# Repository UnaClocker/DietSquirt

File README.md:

# DietSquirt
Version 4.0 PCB Update October 2026
Migrated to KiCad 10.0, no more legacy Eagle requirements. The board is a 4 layer 100x100mm PCB now. Updated some components, 
switched to more common and standard sized components. As of the time of this writing, the boards are in production.
Included injector and coil drivers both this time. I know the injector drivers I picked will work with at least 2x 
high impedance injectors each.
I will update as needed with the results of the first test batch. Included the exact gerbers I submitted, but I have
made some minor changes to the silkscreen on the back of the PCB since then. One way or another, I'd like to have a 
functioning PCB to use in a vehicle in the next month, so this version will be fully tested here soon.
B&G actually sent me a cease and desist back when I first released this 10 years ago. Based on some obscure patent.
Well, it's been long enough that a patent would have expired by now. Given they started MegaSquirt around 2002, 
patents only last 17 years and it's going on 25 now... I kept the Anonymous name on there to keep up the rebel
spirit of this thing.
I still have a pile of MS1 CPU's, so this board is still 68hc908 centric. But a minor refactoring would make it 
perfectly happy with the MS2 CPU module or even MS3.

--- Old notes circa 2017 ---

Low cost DIY open source MegaSquirt derivative.

Welcome to my incomplete project. This was meant to be a much cheaper 
alternative to MegaSquirt. It uses the same processor as the MegaSquirt,
which is wired the same way as you might wire it for MegaSquirt-Extra 
firmware. Now being that this is not a licensed board, you shouldn’t run 
their firmware on it. But if you do, who am I to stop you. ;) You’re not 
supposed to run MegaSquirt on street cars either, but most MegaSquirt users 
do.

Please watch the video about this: https://www.youtube.com/watch?v=LJTZ3sH1d-M

This project is licensed under the BSD License. Take it and do anything with
it. If you mass produce and sell it, I hope you’re not using the MegaSquirt 
firmware, their lawyers will bury you. Your own personal use, totally another 
matter, not worth coming after Joe Blow who’s running it in their own car. 
Ideally, the MegaSquirt firmware can prove the board, then we can switch to 
a far better processor and far more open firmware like the STM32F4 with 
RusEFI firmware. I signed the board “Anonymous” because of the risk of 
B&G’s lawyers. 

As stated, this board is a work in progress. I’d like to say I can come 
back and finish it, but I designed it two years ago, maybe 2 1/2 years at 
this point. Right after that I discovered my wife was having an affair 
(TMI…), and entered a long drawn out divorce. Now I’m a single father of 
two kids so I don’t have much time to devote to these projects anymore. 
I’m placing the files on Github, we can work together to update and fix 
the board as testing progresses.
Current known issues: 
	The components for the voltage regulator circuit are too big and 
don’t fit. Namely the capacitors. 
	It needs the LC filter added between the output of the VR and the 
rest of the board to clean up the noise from the switch mode power supply. 
See the data sheet to the 34063 voltage regulator for that circuit.
	The DB15 and DB25 connectors are too far inboard, they need to be 
shifted out to the next mark on the silkscreen.

Next up, this board does not have onboard injector drivers. I had intended 
it to use the JBPerf P&H board. He seems to have stopped selling it since 
then, so I, or someone else may need to create a clone of his old board. 
It’s a very very simple circuit board to make. The chips are still available.

You can submit the .brd files to OSHPark.com to have 3 copies of the board 
made. It’s VERY expensive there. but if you’re in the US, they’re very fast. 
You can get 10 boards made at www.elecrow.com, under their 5cmx10cm pricing, 
I believe it’s $20 for 10 boards. Give the spare boards to friends, or save 
them as spares. Don’t sell them, you’ll risk the wrath of the B&G lawyers.

See the attached BOM for the list of parts you’ll want to order from Digikey 
for this board.

The files are for Eagle. Place the .brd and .sch files in a DietSquirt folder
under your main eagle projects, then load the .sch schematic file and .brd board 
layout file. The gerbers are included, but since the board needs work still, 
I wouldn't suggest building having it produced. At the very least, you'd have 
to run an external 5v voltage regulator. I'd have prefered to have done the 
board in KiCad, but I knew Eagle better at the time. You can get a free version 
of Eagle, google it, download it. Works in all 3 major OS's.

I’m probably forgetting a lot. I’ll document more as time allows. 
Questions? unaclocker@gmail.com

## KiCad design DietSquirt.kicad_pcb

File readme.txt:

Welcome to my incomplete project. This was meant to be a much cheaper 
alternative to MegaSquirt. It uses the same processor as the MegaSquirt,
which is wired the same way as you might wire it for MegaSquirt-Extra 
firmware. Now being that this is not a licensed board, you shouldn’t run 
their firmware on it. But if you do, who am I to stop you. ;) You’re not 
supposed to run MegaSquirt on street cars either, but most MegaSquirt users 
do.
Please watch the video about this which will be posted on YouTube shortly.
This project is licensed under the BSD License. Take it and do anything with
it. If you mass produce and sell it, I hope you’re not using the MegaSquirt 
firmware, their lawyers will bury you. Your own personal use, totally another 
matter, not worth coming after Joe Blow who’s running it in their own car. 
Ideally, the MegaSquirt firmware can prove the board, then we can switch to 
a far better processor and far more open firmware like the STM32F4 with 
RusEFI firmware. I signed the board “Anonymous” because of the risk of 
B&G’s lawyers. 
As stated, this board is a work in progress. I’d like to say I can come 
back and finish it, but I designed it two years ago, maybe 2 1/2 years at 
this point. Right after that I discovered my wife was having an affair 
(TMI…), and entered a long drawn out divorce. Now I’m a single father of 
two kids so I don’t have much time to devote to these projects anymore. 
I’m placing the files on Github, we can work together to update and fix 
the board as testing progresses.
Current known issues: 
	The components for the voltage regulator circuit are too big and 
don’t fit. Namely the capacitors. 
	It needs the LC filter added between the output of the VR and the 
rest of the board to clean up the noise from the switch mode power supply. 
See the data sheet to the 34063 voltage regulator for that circuit.
	The DB15 and DB25 connectors are too far inboard, they need to be 
shifted out to the next mark on the silkscreen.

Next up, this board does not have onboard injector drivers. I had intended 
it to use the JBPerf P&H board. He seems to have stopped selling it since 
then, so I, or someone else may need to create a clone of his old board. 
It’s a very very simple circuit board to make. The chips are still available.

You can submit the .brd files to OSHPark.com to have 3 copies of the board 
made. It’s VERY expensive there. but if you’re in the US, they’re very fast. 
You can get 10 boards made at www.elecrow.com, under their 5cmx10cm pricing, 
I believe it’s $20 for 10 boards. Give the spare boards to friends, or save 
them as spares. Don’t sell them, you’ll risk the wrath of the B&G lawyers.

See the attached BOM for the list of parts you’ll want to order from Digikey 
for this board.

The files are for Eagle. Load the .pro project file, then load the .sch 
schematic file and .brd board layout file. The gerbers are included, but 
since the board needs work still, I wouldn't suggest building it. At the 
very least, you'd have to run an external 5v voltage regulator. I'd have 
prefered to have done the board in KiCad,
but I knew Eagle better at the time. You can get a free version of Eagle, 
google it, download it. Works in all 3 major OS's.

I’m probably forgetting a lot. I’ll document more as time allows. 
Questions? unaclocker@gmail.com

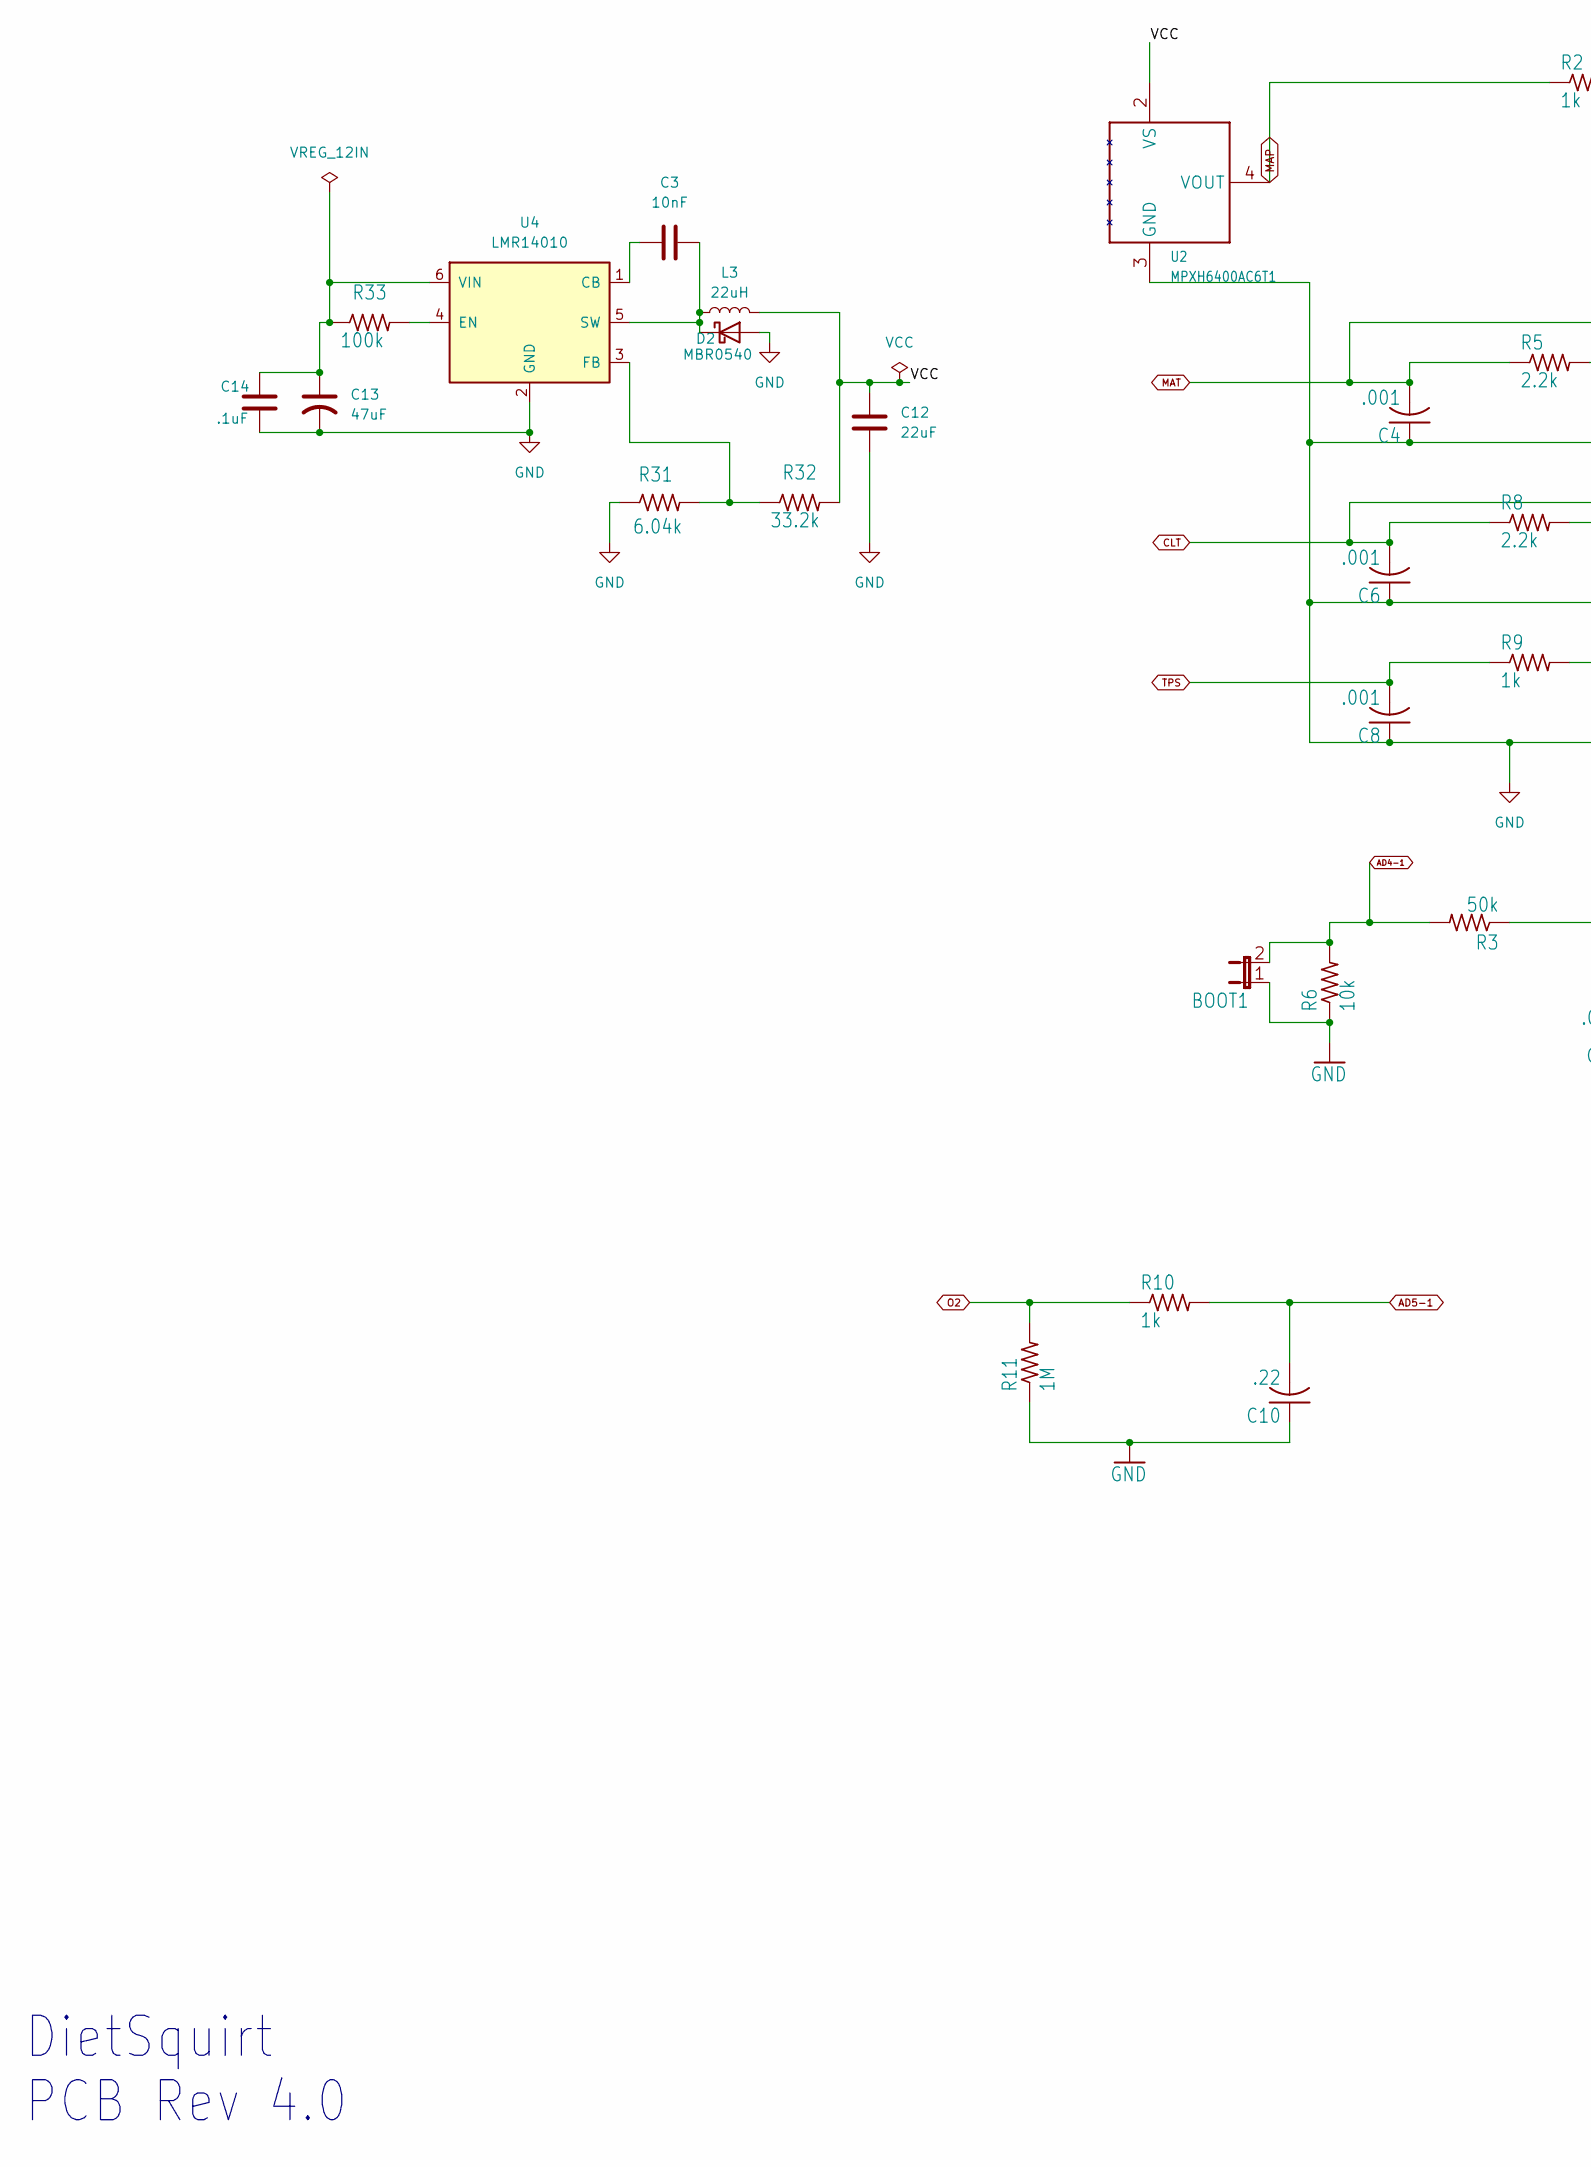
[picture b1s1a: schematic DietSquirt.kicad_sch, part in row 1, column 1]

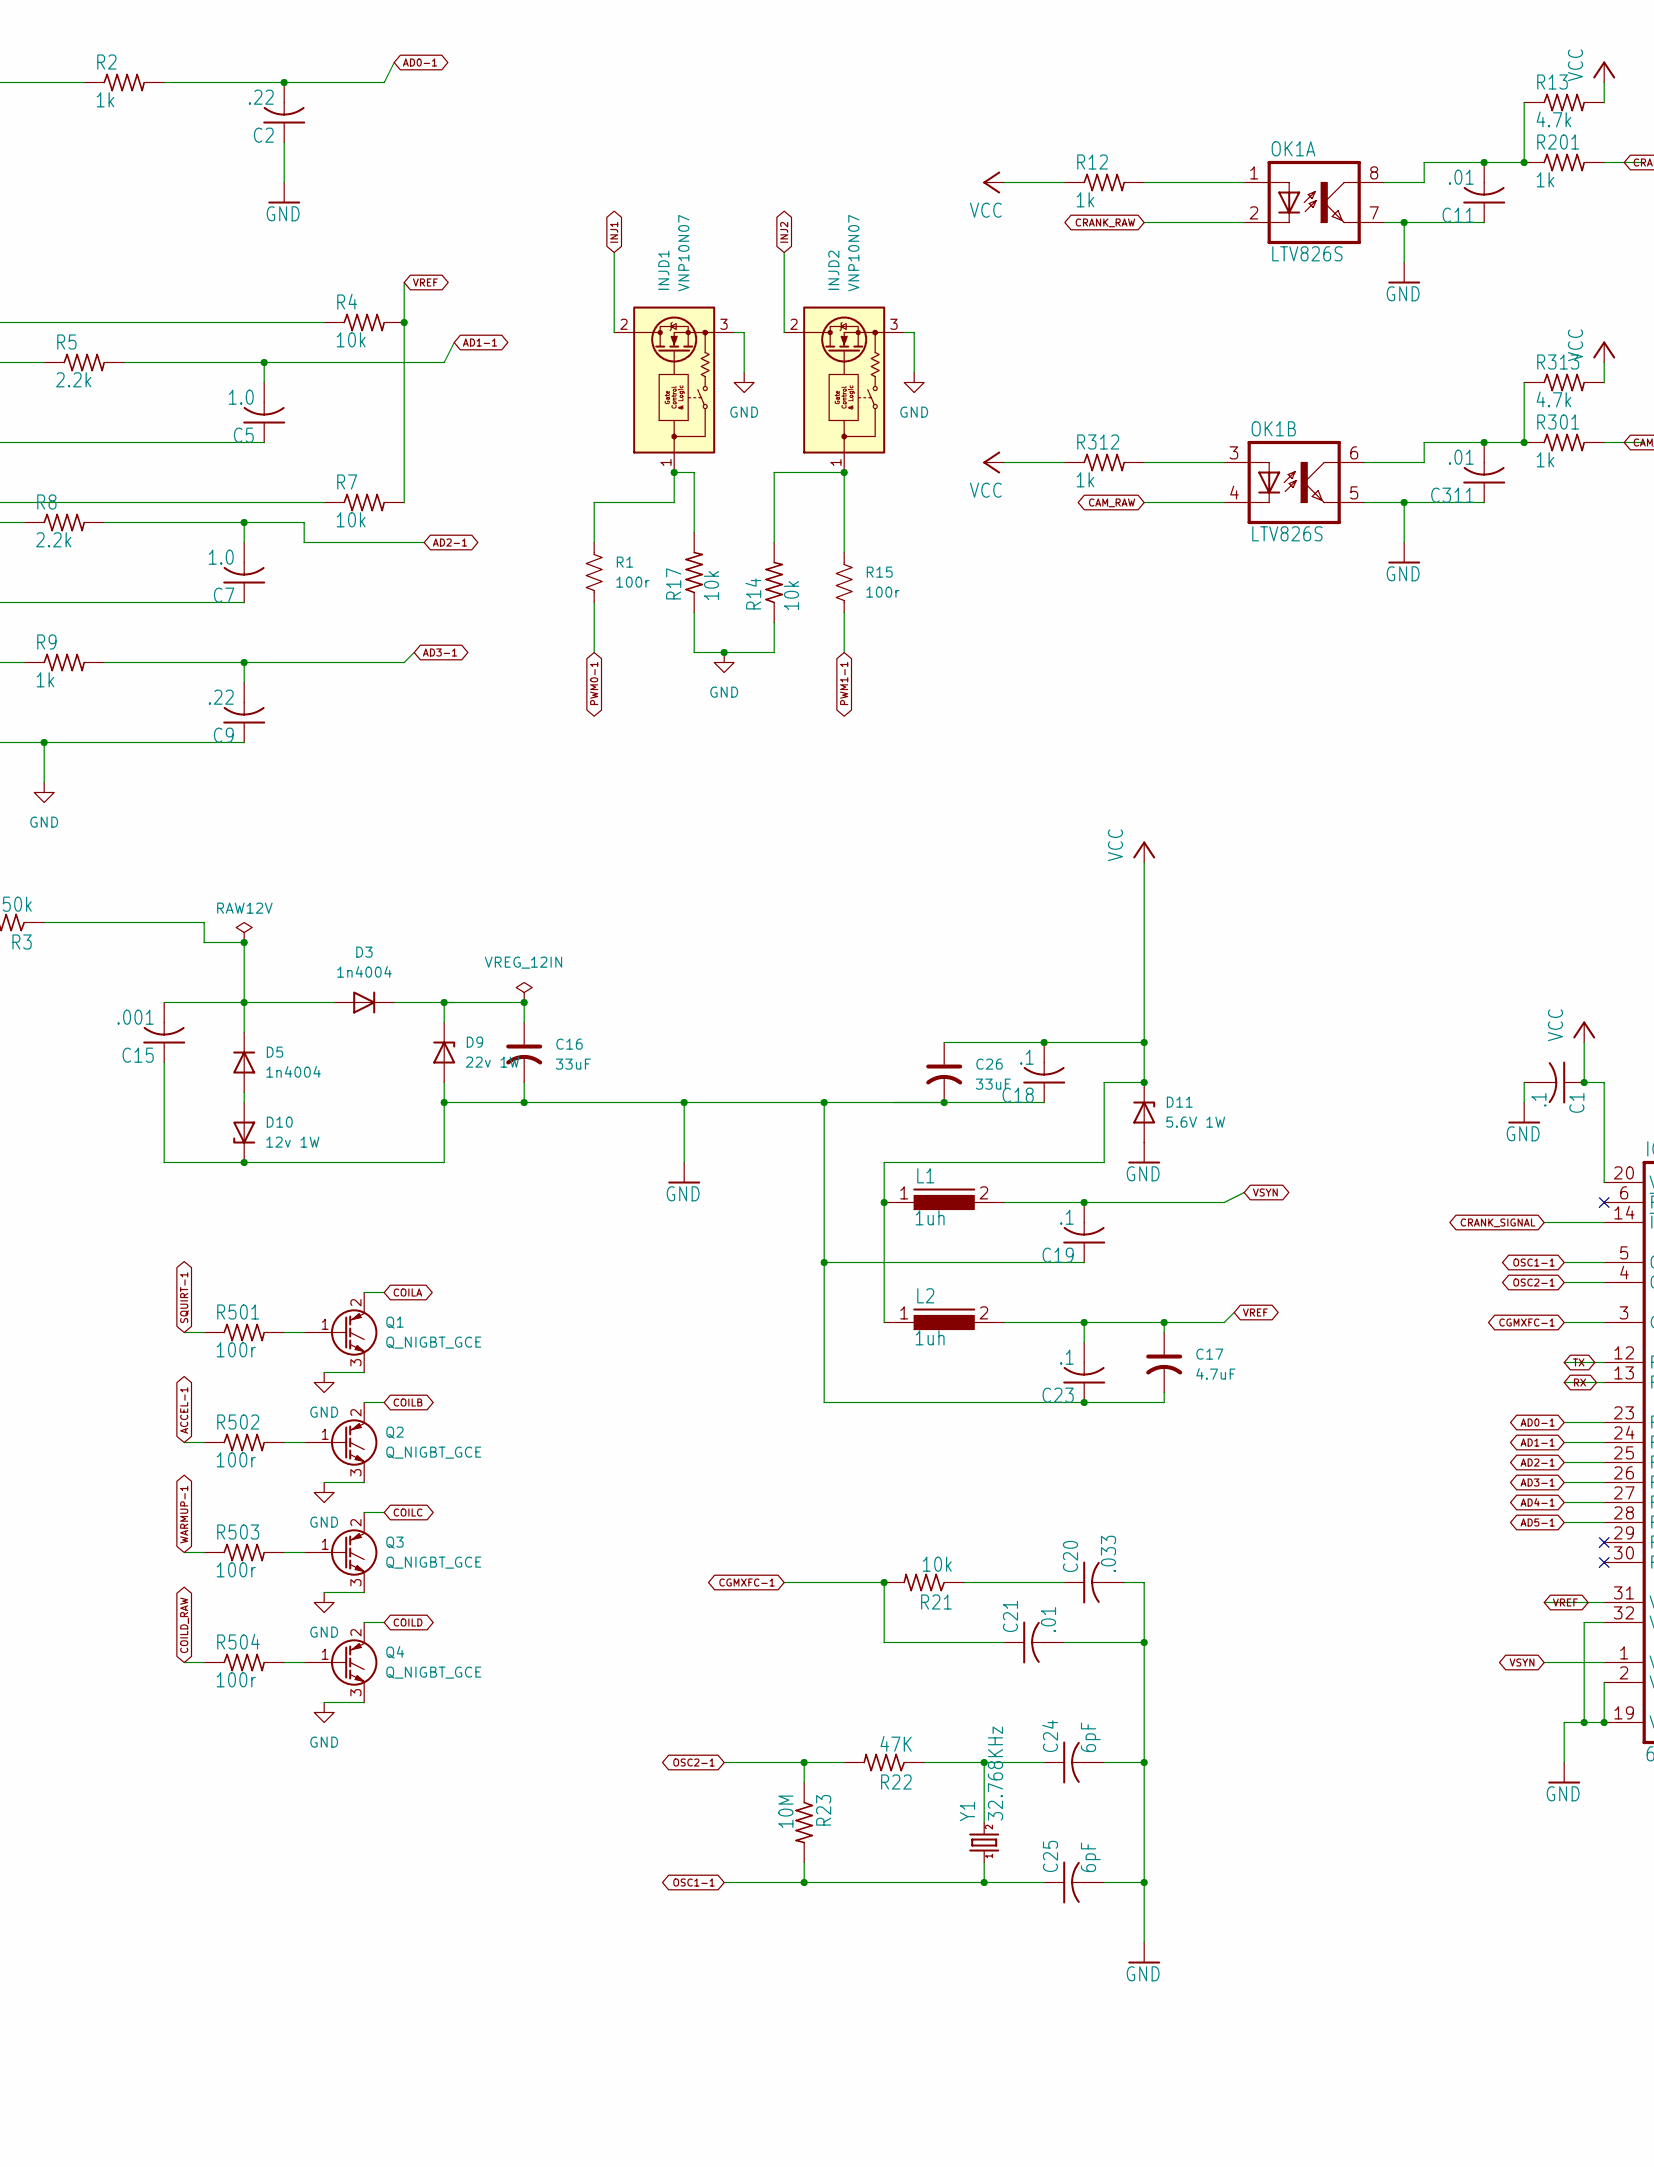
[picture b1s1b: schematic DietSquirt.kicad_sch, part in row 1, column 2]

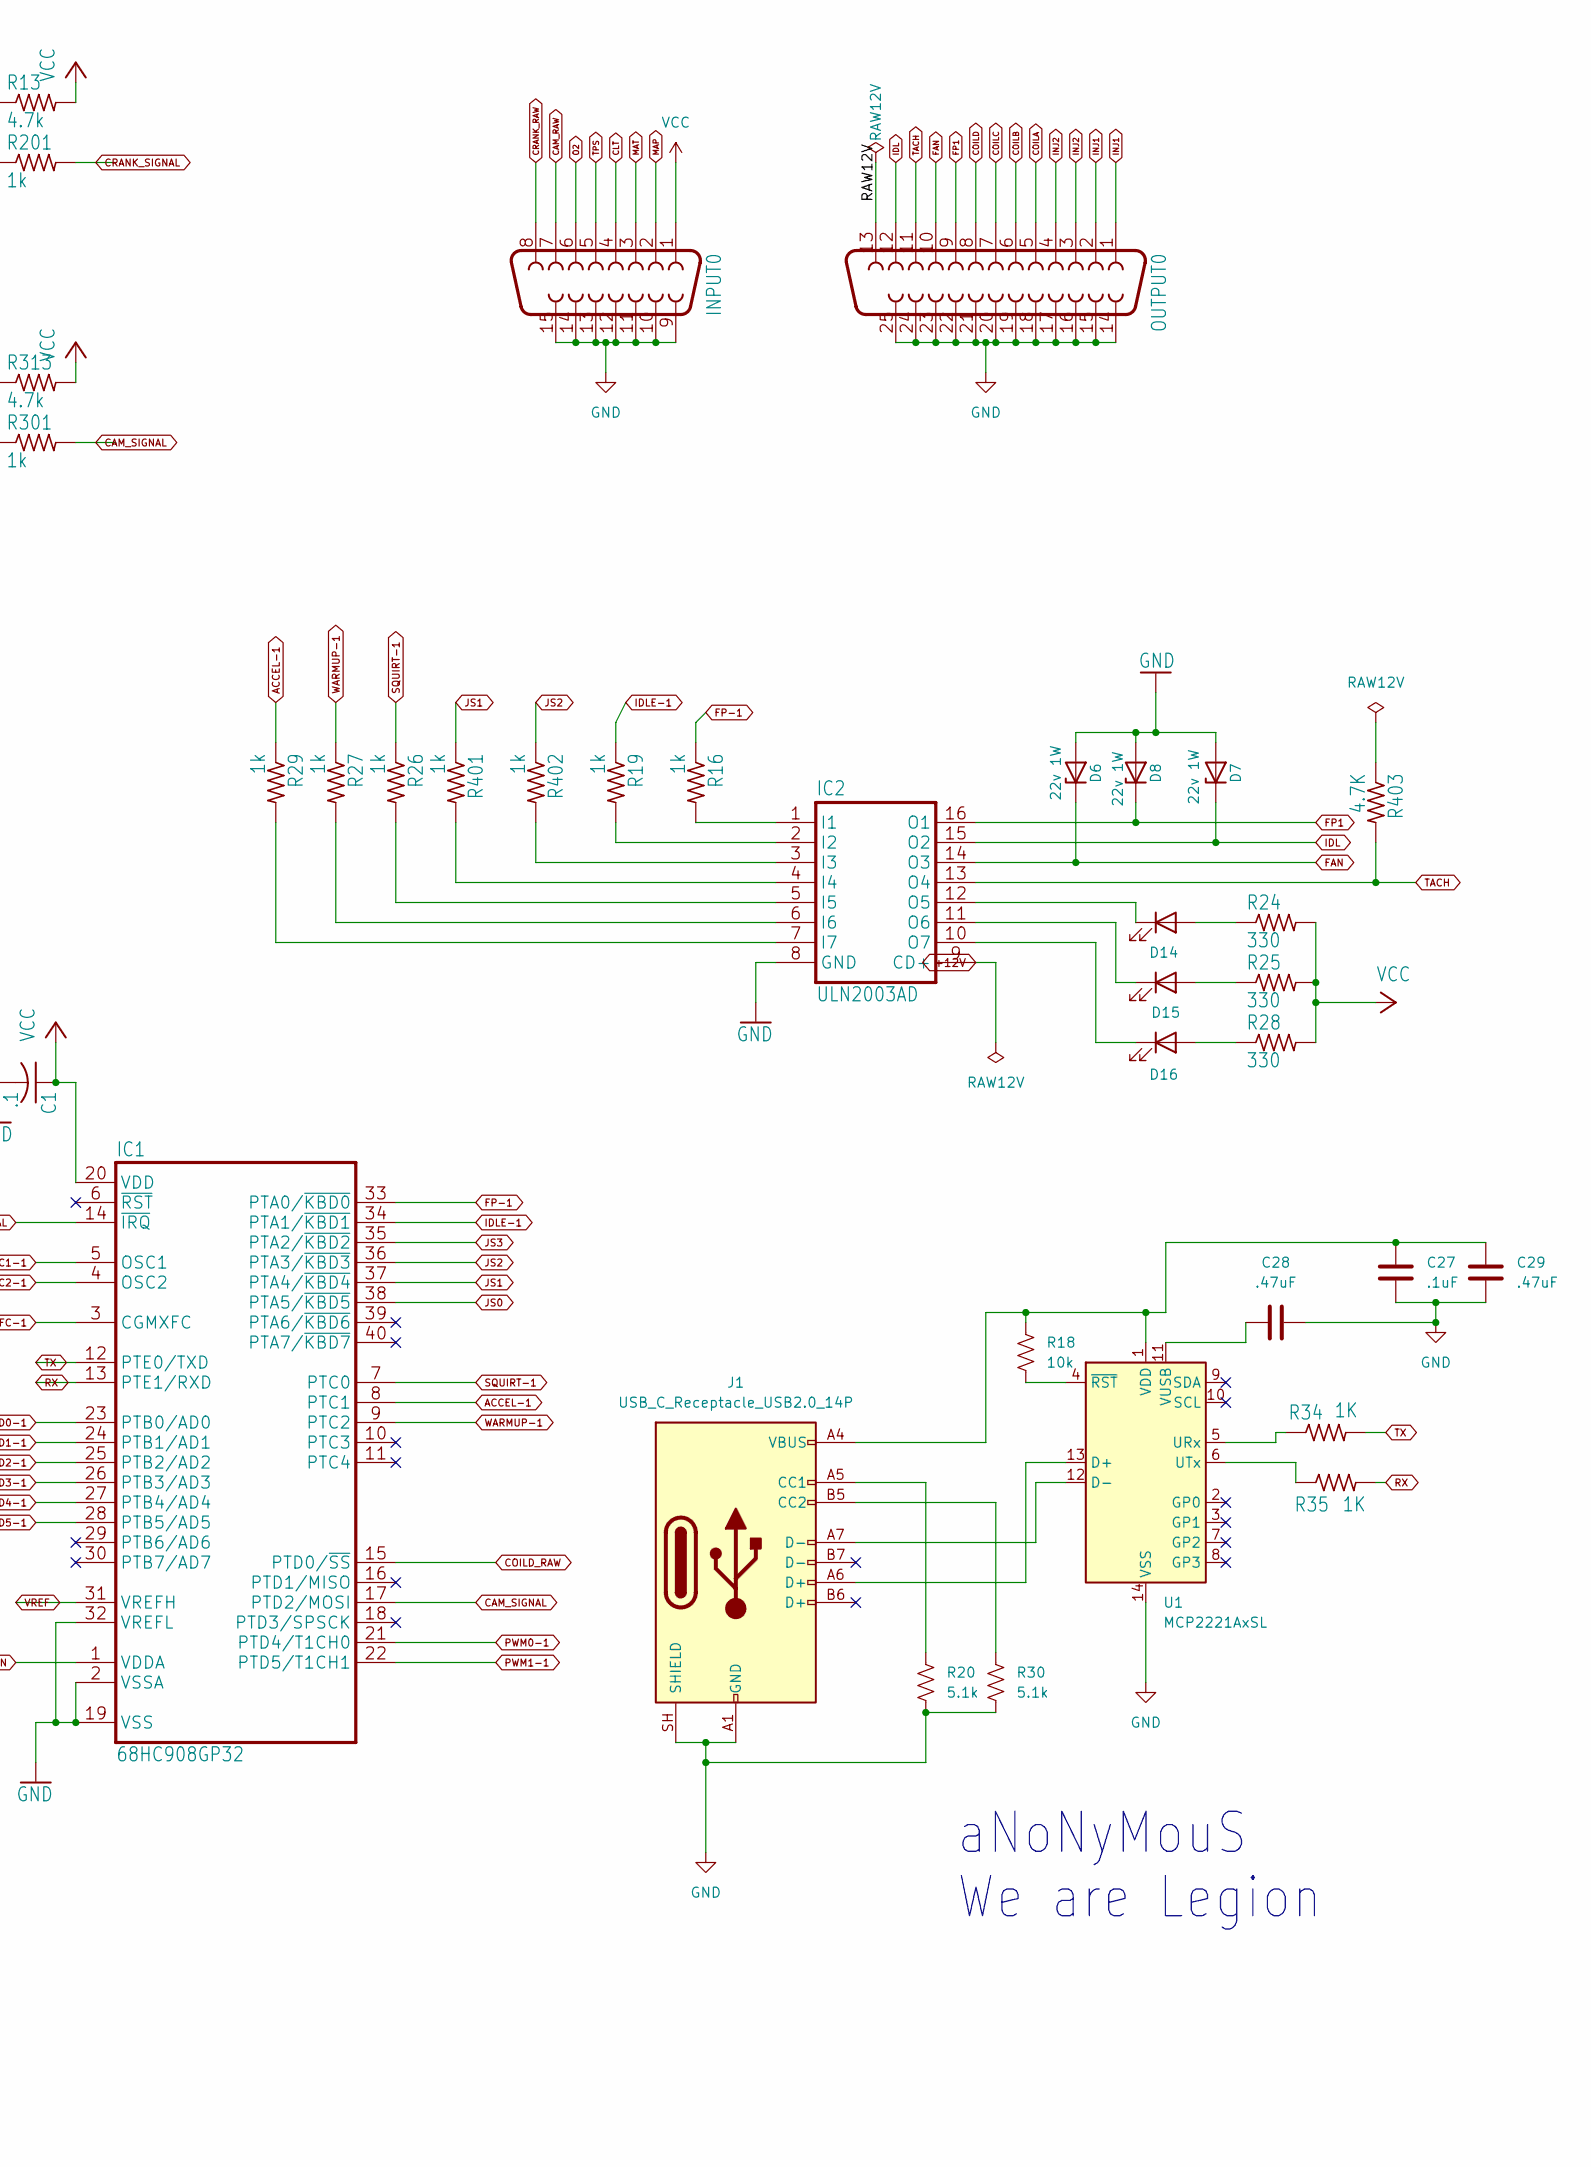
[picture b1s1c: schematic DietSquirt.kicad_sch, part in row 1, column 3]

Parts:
BOOT1: JUMPER-2PTH; PinHeader_1x02_P1.00mm_Horizontal
C1, C18, C19, C23: .1; C_0805_2012Metric_Pad1.18x1.45mm_HandSolder
C2, C9, C10: .22; C_0805_2012Metric_Pad1.18x1.45mm_HandSolder
C3: 10nF; C_0805_2012Metric_Pad1.18x1.45mm_HandSolder
C4, C6, C8, C15: .001; C_0805_2012Metric_Pad1.18x1.45mm_HandSolder
C5, C7: 1.0; C_0805_2012Metric_Pad1.18x1.45mm_HandSolder
C11, C21, C311: .01; C_0805_2012Metric_Pad1.18x1.45mm_HandSolder
C12: 22uF; C_0805_2012Metric_Pad1.18x1.45mm_HandSolder
C13: 47uF; CP_Elec_4x4.5
C14, C27: .1uF; C_0805_2012Metric_Pad1.18x1.45mm_HandSolder
C16, C26: 33uF; CP_Elec_4x4.5
C17: 4.7uF; CP_Elec_4x4.5
C20: .033; C_0805_2012Metric_Pad1.18x1.45mm_HandSolder
C24, C25: 6pF; C_0805_2012Metric_Pad1.18x1.45mm_HandSolder
C28, C29: .47uF; C_0805_2012Metric_Pad1.18x1.45mm_HandSolder
D2: MBR0540; D_SOD-123
D3, D5: 1n4004; D_SMA
D6, D7, D8, D9: 22v 1W; D_SMA
D10: 12v 1W; D_SMA
D11: 5.6V 1W; D_SMA
D14, D15, D16: LED; LED_0805_2012Metric
IC1: 68HC908GP32; DIP-40_W15.24mm; MPN MC68HC908GP32CP
IC2: ULN2003AD; SOIC-16_3.9x9.9mm_P1.27mm
INJD1, INJD2: VNP10N07; TO-220-3_Vertical
INPUT0: F15H; DSUB-15_Socket_EdgeMount_P2.77mm
J1: USB_C_Receptacle_USB2.0_14P; USB_C_Receptacle_GCT_USB4085
L1, L2: 1uh; L_Taiyo-Yuden_NR-50xx
L3: 22uH; L_Taiyo-Yuden_NR-50xx
OK1: LTV826S; DIP-8_W8.89mm_SMDSocket_LongPads
OUTPUT0: F25H; DSUB-25_Pins_EdgeMount_P2.77mm
Q1, Q2, Q3, Q4: Q_NIGBT_GCE; TO-263-2
R1, R15: 100r; R_0805_2012Metric_Pad1.20x1.40mm_HandSolder
R2, R9, R10, R12, R16, R19: 1k; R_0805_2012Metric_Pad1.20x1.40mm_HandSolder
R3: 50k; R_0805_2012Metric_Pad1.20x1.40mm_HandSolder
R4, R6, R7, R14, R17, R18: 10k; R_0805_2012Metric_Pad1.20x1.40mm_HandSolder
R5, R8: 2.2k; R_0805_2012Metric_Pad1.20x1.40mm_HandSolder
R11: 1M; R_0805_2012Metric_Pad1.20x1.40mm_HandSolder
R13: 4.7k; R_0805_2012Metric_Pad1.20x1.40mm_HandSolder
R20: 5.1k; R_0805_2012Metric_Pad1.20x1.40mm_HandSolder
R21: 10k; R_0805_2012Metric
R22: 47K; R_0805_2012Metric
R23: 10M; R_0805_2012Metric
R24, R25, R28: 330; R_0805_2012Metric
R26, R27, R29, R201, R301, R312, R401, R402: 1k; R_0805_2012Metric
R30: 5.1k; R_0805_2012Metric
R31: 6.04k; R_0805_2012Metric
R32: 33.2k; R_0805_2012Metric
R33: 100k; R_0805_2012Metric
R34, R35: 1K; R_0805_2012Metric_Pad1.20x1.40mm_HandSolder
R313: 4.7k; R_0805_2012Metric
R403: 4.7K; R_0805_2012Metric
R501, R502, R503, R504: 100r; R_0805_2012Metric
U1: MCP2221AxSL; SOIC-14_3.9x8.7mm_P1.27mm
U2: MPXH6400AC6T1; SOIC-8_7.5x5.85mm_P1.27mm
U4: LMR14010; SOT-23-6
Y1: 32.768KHz; Crystal_SMD_3215-2Pin_3.2x1.5mm

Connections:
+12V: IC2.9 (CD+)
/RAW12V: OUTPUT0.13
ACCEL-1: IC1.8 (PTC1), R29.1, R502.1
AD0-1: C2.2, IC1.23 (PTB0/AD0), R2.2
AD1-1: C5.2, IC1.24 (PTB1/AD1), R5.2
AD2-1: C7.2, IC1.25 (PTB2/AD2), R8.2
AD3-1: C9.2, IC1.26 (PTB3/AD3), R9.2
AD4-1: BOOT1.2, IC1.27 (PTB4/AD4), R3.2, R6.2
AD5-1: C10.2, IC1.28 (PTB5/AD5), R10.2
CAM_RAW: INPUT0.7, OK1.4 (C)
CAM_SIGNAL: IC1.17 (PTD2/MOSI), R301.2
CGMXFC-1: C21.1, IC1.3 (CGMXFC), R21.2
CLT: C6.2, INPUT0.4, R7.1, R8.1
COILA: OUTPUT0.5, Q1.2 (C)
COILB: OUTPUT0.6, Q2.2 (C)
COILC: OUTPUT0.7, Q3.2 (C)
COILD: OUTPUT0.8, Q4.2 (C)
COILD_RAW: IC1.15 (PTD0/~SS), R504.1
CRANK_RAW: INPUT0.8, OK1.2 (C)
CRANK_SIGNAL: IC1.14 (~IRQ), R201.2
FAN: D6.1 (K), IC2.14 (O3), OUTPUT0.10
FP1: D8.1 (K), IC2.16 (O1), OUTPUT0.9
FP-1: IC1.33 (PTA0/~KBD0), R16.1
GND: BOOT1.1, C1.2, C2.1, C4.1, C5.1, C6.1, C7.1, C8.1, C9.1, C10.1, C11.1, C12.2, C13.2, C14.2, C15.1, C16.2, C17.2, C18.1, C19.1, C20.2, C21.2, C23.1, C24.2, C25.2, C26.2, C27.2, C28.2, C29.2, C311.1, D2.2 (A), D6.2 (A), D7.2 (A), D8.2 (A), D9.2 (A), D10.1 (K), D11.2 (A), IC1.2 (VSSA), IC1.19 (VSS), IC1.32 (VREFL), IC2.8 (GND), INJD1.3 (SOURCE), INJD2.3 (SOURCE), INPUT0.9, INPUT0.10, INPUT0.11, INPUT0.12, INPUT0.13, INPUT0.14, INPUT0.15, J1.A1 (GND), J1.A12 (GND), J1.B1 (GND), J1.B12 (GND), J1.SH (SHIELD), OK1.5 (EMIT), OK1.7 (EMIT), OUTPUT0.14, OUTPUT0.15, OUTPUT0.16, OUTPUT0.17, OUTPUT0.18, OUTPUT0.19, OUTPUT0.20, OUTPUT0.21, OUTPUT0.22, OUTPUT0.23, OUTPUT0.24, OUTPUT0.25, Q1.3 (E), Q2.3 (E), Q3.3 (E), Q4.3 (E), R6.1, R11.1, R14.1, R17.1, R20.2, R30.2, R31.1, U1.14 (VSS), U2.3 (GND), U4.2 (GND)
IDL: D7.1 (K), IC2.15 (O2), OUTPUT0.12
IDLE-1: IC1.34 (PTA1/~KBD1), R19.1
INJ1: INJD1.2 (DRAIN), OUTPUT0.1, OUTPUT0.2
INJ2: INJD2.2 (DRAIN), OUTPUT0.3, OUTPUT0.4
JS0: IC1.38 (PTA5/~KBD5)
JS1: IC1.37 (PTA4/~KBD4), R401.1
JS2: IC1.36 (PTA3/~KBD3), R402.1
JS3: IC1.35 (PTA2/~KBD2)
MAP: INPUT0.2, R2.1, U2.4 (VOUT)
MAT: C4.2, INPUT0.3, R4.1, R5.1
unnamed: C20.1, R21.1
unnamed: C24.1, R22.1, Y1.2
unnamed: C3.2, D2.1 (K), L3.1, U4.5 (SW)
unnamed: C15.2, D3.2 (A), D5.1 (K), R3.1
unnamed: C16.1, D3.1 (K), D9.1 (K)
unnamed: D5.2 (A), D10.2 (A)
unnamed: D14.2 (A), R24.1
unnamed: D14.1 (K), IC2.12 (O5)
unnamed: D15.2 (A), R25.1
unnamed: D15.1 (K), IC2.11 (O6)
unnamed: D16.2 (A), R28.1
unnamed: D16.1 (K), IC2.10 (O7)
unnamed: IC2.1 (I1), R16.2
unnamed: IC2.2 (I2), R19.2
unnamed: IC2.3 (I3), R402.2
unnamed: IC2.4 (I4), R401.2
unnamed: IC2.5 (I5), R26.2
unnamed: IC2.6 (I6), R27.2
unnamed: IC2.7 (I7), R29.2
unnamed: INJD1.1 (INPUT), R1.1, R17.2
unnamed: INJD2.1 (INPUT), R14.2, R15.1
unnamed: J1.A5 (CC1), R20.1
unnamed: J1.B5 (CC2), R30.1
unnamed: OK1.1 (A), R12.2
unnamed: C11.2, OK1.8 (COL), R13.1, R201.1
unnamed: OK1.3 (A), R312.2
unnamed: C311.2, OK1.6 (COL), R301.1, R313.1
unnamed: Q1.1 (G), R501.2
unnamed: Q2.1 (G), R502.2
unnamed: Q3.1 (G), R503.2
unnamed: Q4.1 (G), R504.2
unnamed: J1.A6 (D+), U1.13 (D+)
unnamed: J1.A7 (D-), U1.12 (D-)
unnamed: R34.1, U1.5 (URx)
unnamed: R35.1, U1.6 (UTx)
unnamed: C27.1, C29.1, J1.A4 (VBUS), J1.A9 (VBUS), J1.B4 (VBUS), J1.B9 (VBUS), R18.1, U1.1 (VDD)
unnamed: C28.1, U1.11 (VUSB)
unnamed: R18.2, U1.4 (~RST)
unnamed: C3.1, U4.1 (CB)
unnamed: R33.2, U4.4 (EN)
unnamed: R31.2, R32.1, U4.3 (FB)
unnamed: C13.1, C14.1, R33.1, U4.6 (VIN)
O2: INPUT0.6, R10.1, R11.2
OSC1-1: C25.1, IC1.5 (OSC1), R23.2, Y1.1
OSC2-1: IC1.4 (OSC2), R22.2, R23.1
PWM0-1: IC1.21 (PTD4/T1CH0), R1.2
PWM1-1: IC1.22 (PTD5/T1CH1), R15.2
RX: IC1.13 (PTE1/RXD), R35.2
SQUIRT-1: IC1.7 (PTC0), R26.1, R501.1
TACH: IC2.13 (O4), OUTPUT0.11, R403.2
TPS: C8.2, INPUT0.5, R9.1
TX: IC1.12 (PTE0/TXD), R34.2
VCC: C1.1, C12.1, C18.2, C26.1, D11.1 (K), IC1.20 (VDD), INPUT0.1, L1.1, L2.1, L3.2, R12.1, R13.2, R24.2, R25.2, R28.2, R32.2, R312.1, R313.2, U2.2 (VS)
VREF: C17.1, C23.2, IC1.31 (VREFH), L2.2, R4.2, R7.2
VSYN: C19.2, IC1.1 (VDDA), L1.2
WARMUP-1: IC1.9 (PTC2), R27.1, R503.1

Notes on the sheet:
DietSquirt PCB Rev 4.0
aNoNyMouS We are Legion~{}

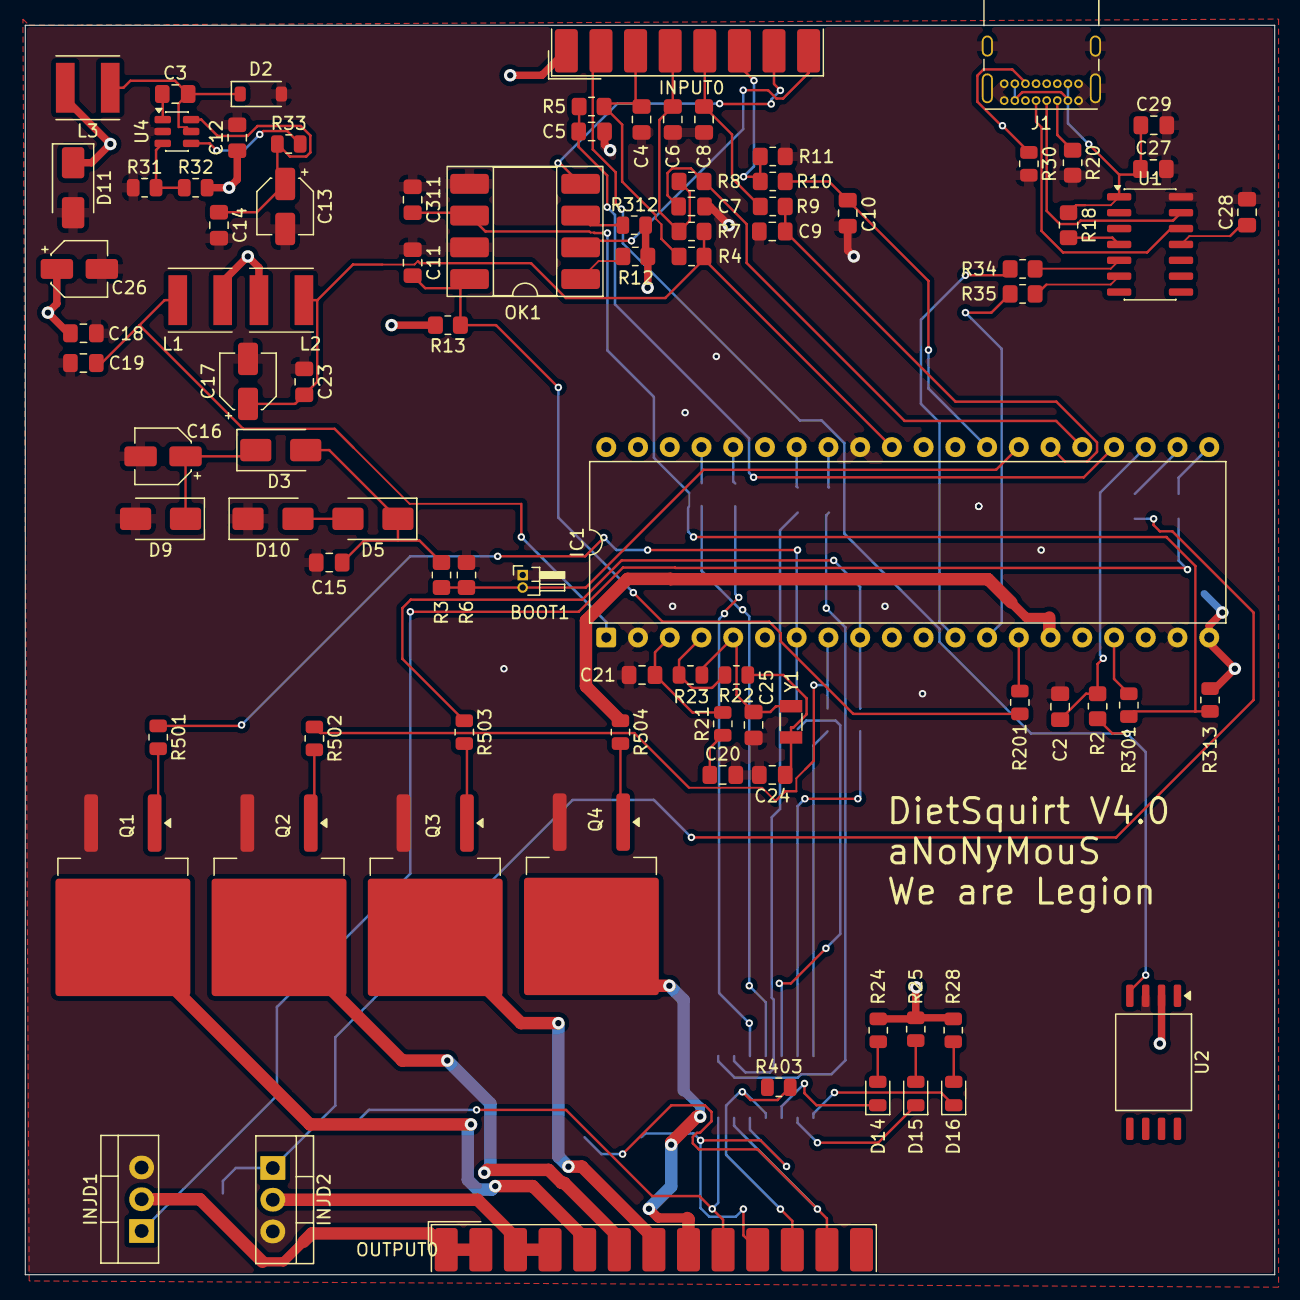
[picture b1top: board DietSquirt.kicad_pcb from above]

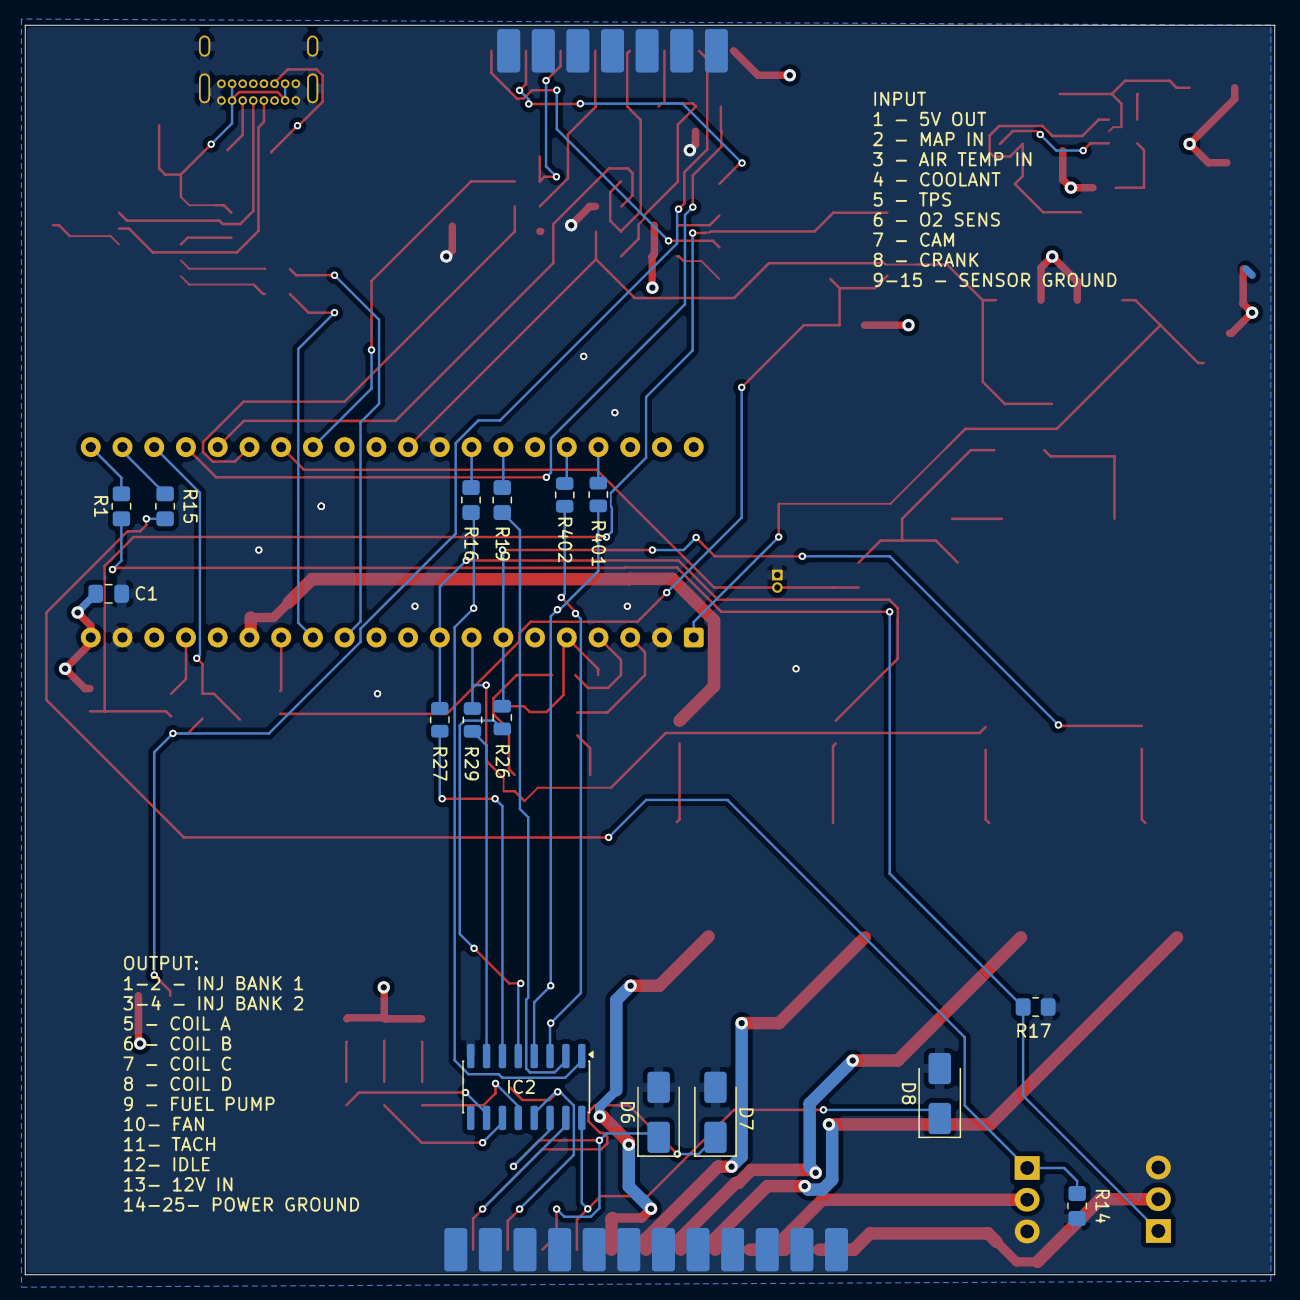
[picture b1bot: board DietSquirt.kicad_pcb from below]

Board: 4 copper layers, 100.0 x 100.0 mm, 107 parts (16 on the bottom side), 86 nets.
